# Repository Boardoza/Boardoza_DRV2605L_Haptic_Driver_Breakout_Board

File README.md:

# Boardoza DRV2605L Haptic Motor Driver Breakout Board

The **Boardoza DRV2605L Haptic Driver Breakout Board** is based on the **Texas Instruments DRV2605L**, a powerful and intelligent haptic motor driver designed specifically for **ERM (Eccentric Rotating Mass)** and **LRA (Linear Resonant Actuator)** vibration motors. Unlike simple on/off motor drivers, the DRV2605L integrates a built-in waveform library and smart-loop control engine to generate advanced vibration effects such as clicks, double-clicks, ramps, buzz patterns, and audio-synchronized feedback.

Unlike standard motor drivers for DC or stepper motors, the DRV2605 is optimized for **ERM (Eccentric Rotating Mass)** and **LRA (Linear Resonant Actuator)** motors. It communicates via **I²C**, allowing you to configure, chain, and trigger complex vibration patterns directly from your microcontroller. This breakout board is ideal for **wearables, game controllers, touch interfaces, mobile devices, assistive systems, and any project that requires professional-grade haptic feedback**.

## [Click here to purchase!](https://www.ozdisan.com/ureticiler/boardoza)

| Front Side | Back Side |
|:---:|:---:|
|  |  |

---

## Key Features
 
- **I²C-Controlled Digital Playback Engine:** Includes a waveform sequencer for flexible haptic pattern generation.  
- **Real-Time Playback Options:** Supports control via I²C, PWM, or analog input.  
- **Dual Drive Modes:** Operates in open-loop (ERM) and closed-loop (LRA) configurations.  
- **Smart-Loop™ Control:** Provides automatic overdrive and braking for optimized performance.  
- **Automatic Resonance Tracking:** Includes actuator diagnostics for LRA operation.  
- **Automatic Level Calibration:** Ensures consistent output performance.  
- **Battery Voltage Compensation:** Maintains stable operation under varying supply conditions.  
- **Differential H-Bridge Output:** Features OUT+ and OUT− for driving actuators.    

---

## Technical Specifications

**Model:** DRV2605L  
**Manufacturer:** Boardoza  
**Manufacturer IC:** Texas Instruments  
**Device Type:** Haptic Driver IC  
**Functions:** Smart Haptic Motor Driver    
**Input Voltage (VDD):** 2.0V – 5.2V  
**Interface:** I²C (Standard & Fast Mode, up to 400kHz)  
**Control Input (IN/TRIG):** PWM / Analog / External Trigger (Selectable)  
**Supported Actuators:**  
- ERM (Eccentric Rotating Mass) – Open-Loop Drive  
- LRA (Linear Resonant Actuator) – Closed-Loop with Auto Resonance Tracking  

**Playback Modes:**  
- Internal ROM Waveform Library  
- RAM-Based Custom Waveform Sequencing  
- Real-Time Playback (RTP) Mode  
- Audio-to-Vibe Mode  

**Drive Output:** Differential H-Bridge (OUT+, OUT−)  
**Auto Features:**  
- Automatic Overdrive & Braking  
- Automatic Resonance Tracking (LRA)  
- Automatic Level Calibration  
- Actuator Diagnostics  

**Operating Temperature:** -40°C to +150°C  
**Board Dimensions:** 20mm x 20mm   

---

## Board Pinout

### ( J1 ) Control & Power Connector

| Pin Number | Pin Name | Description |
|:---:|:---:|---|
| 1 | VCC | Supply Input (2.0V – 5.2V DC) |
| 2 | IN | Multi-mode Input (PWM / Analog / Trigger). Connect to GND if unused |
| 3 | SCL | I²C Serial Clock |
| 4 | SDA | I²C Serial Data |
| 5 | GND | Ground |

### ( J2 ) Haptic Motor Output

| Pin Number | Pin Name | Description |
|:---:|:---:|---|
| 1 | OUT+ | Positive Differential Output |
| 2 | OUT− | Negative Differential Output |

---

## Board Dimensions

---

## Step Files

[Boardoza DRV2605L.step](./assets/DRV2605L%20Step.step)

---

## Datasheet

[DRV2605L Datasheet.pdf](./assets/DRV2605L%20Datasheet.pdf)

---

## Version History

- V1.0.0 - Initial Release  

---

## Support

- If you have any questions or need support, please contact **support@boardoza.com**

---

## **License**

This repository contains both hardware and software components:

### **Hardware Design**

[![CC BY-SA 4.0][cc-by-sa-shield]][cc-by-sa]

All hardware design files are licensed under [Creative Commons Attribution-ShareAlike 4.0 International License][cc-by-sa].

[cc-by-sa]: http://creativecommons.org/licenses/by-sa/4.0/
[cc-by-sa-shield]: https://img.shields.io/badge/License-CC%20BY--SA%204.0-lightgrey.svg

### **Software/Firmware**

[![BSD-3-Clause][bsd-shield]][bsd]

All software and firmware are licensed under [BSD 3-Clause License][bsd].

[bsd]: https://opensource.org/licenses/BSD-3-Clause
[bsd-shield]: https://img.shields.io/badge/License-BSD%203--Clause-blue.svg

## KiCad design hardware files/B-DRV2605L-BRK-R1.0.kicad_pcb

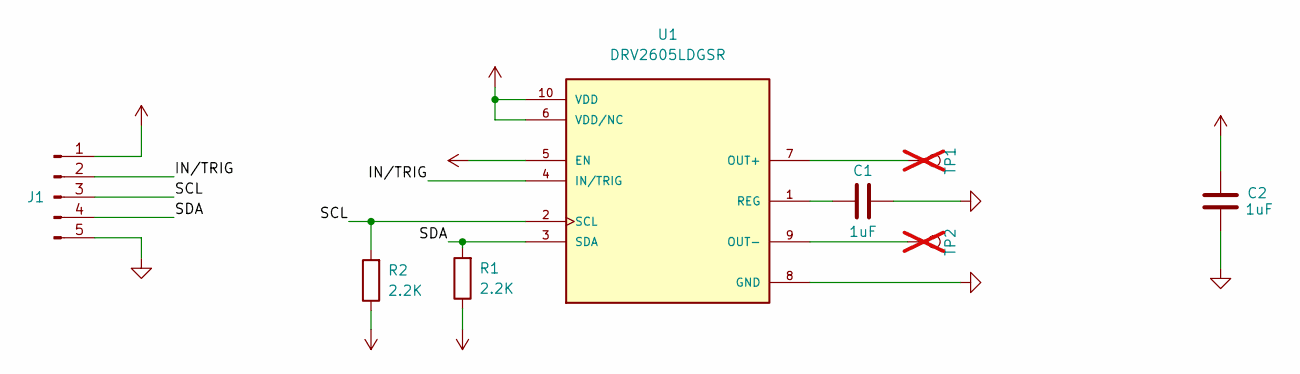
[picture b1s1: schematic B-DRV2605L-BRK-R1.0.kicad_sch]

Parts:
C1, C2: 1uF; C_0603_1608Metric; MPN CL10A105KO8NNNC
J1: Conn_01x05_Pin; PinHeader_1x05_P2.54mm_Vertical; MPN 5PH1SDA25-105G0NNBL-3X6
R1, R2: 2.2K; R_0603_1608Metric; MPN CRT03F7E2201
TP1, TP2: TestPoint; PinHeader_1x01_P2.54mm_Vertical; not fitted
U1: DRV2605LDGSR; SOP50P490X110-10N; PARTREV D

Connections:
/IN/TRIG: J1.2, U1.4 (IN/TRIG)
/SCL: J1.3, R2.2, U1.2 (SCL)
/SDA: J1.4, R1.2, U1.3 (SDA)
GND: C1.2, C2.1, J1.5, U1.8 (GND)
unnamed: TP1.1, U1.7 (OUT+)
unnamed: TP2.1, U1.9 (OUT-)
unnamed: C1.1, U1.1 (REG)
VCC: C2.2, J1.1, R1.1, R2.1, U1.5 (EN), U1.6 (VDD/NC), U1.10 (VDD)

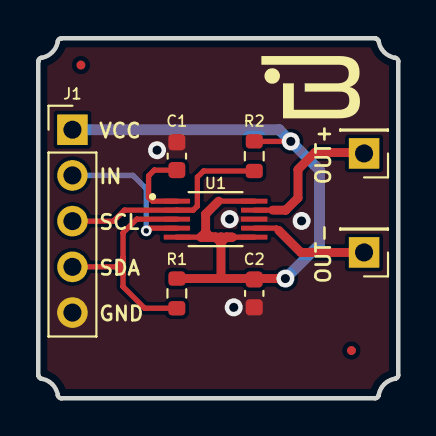
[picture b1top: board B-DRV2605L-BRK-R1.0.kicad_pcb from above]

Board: 2 copper layers, 20.0 x 20.0 mm, 8 parts (0 on the bottom side), 8 nets.

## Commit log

2026-03-18 Update README.md and add license file
2026-04-28 Fixed comment lines
